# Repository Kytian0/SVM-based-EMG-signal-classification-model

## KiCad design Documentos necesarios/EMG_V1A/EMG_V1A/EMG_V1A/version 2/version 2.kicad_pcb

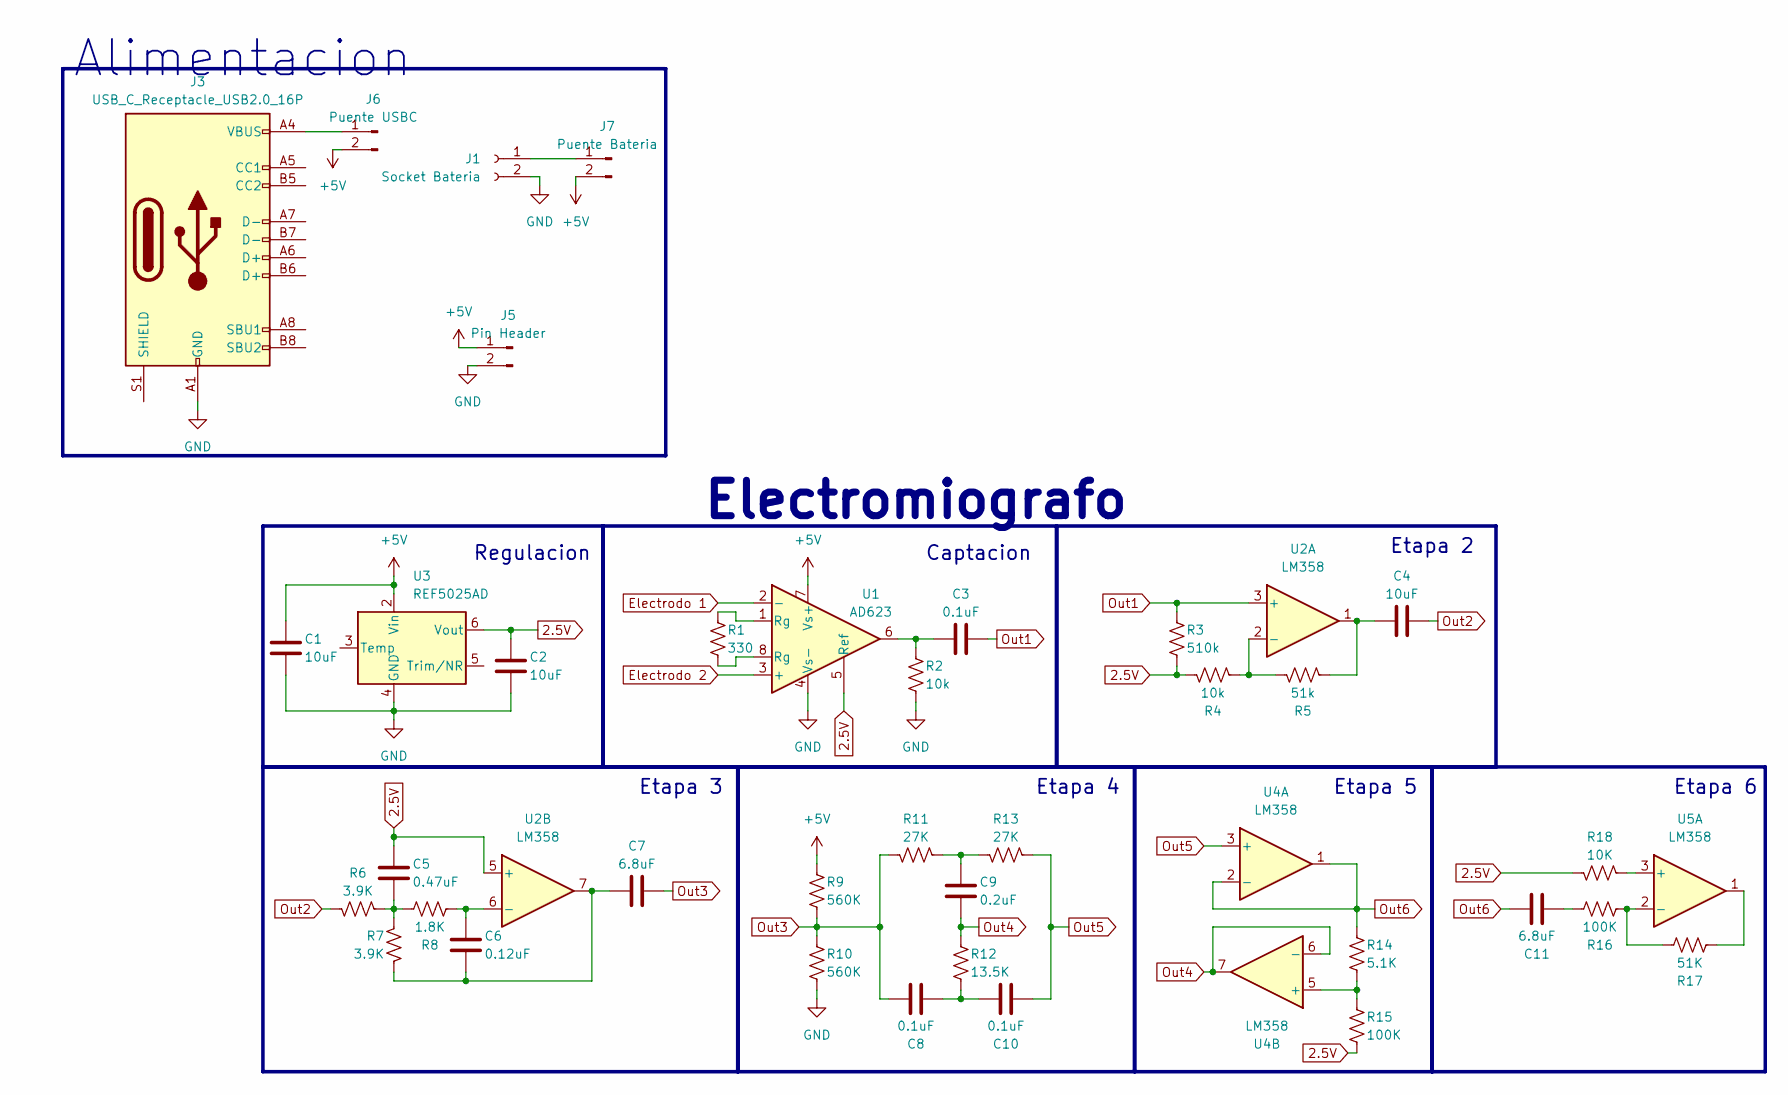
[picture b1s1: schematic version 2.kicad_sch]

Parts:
C1, C2, C4: 10uF; C_Disc_D10.0mm_W2.5mm_P5.00mm
C3, C8, C10: 0.1uF; C_Disc_D10.0mm_W2.5mm_P5.00mm
C5: 0.47uF; C_Disc_D10.0mm_W2.5mm_P5.00mm
C6: 0.12uF; C_Disc_D10.0mm_W2.5mm_P5.00mm
C7, C11: 6.8uF; C_Disc_D10.0mm_W2.5mm_P5.00mm
C9: 0.2uF; C_Disc_D10.0mm_W2.5mm_P5.00mm
J1: Socket Bateria; JST_EH_S2B-EH_1x02_P2.50mm_Horizontal
J3: USB_C_Receptacle_USB2.0_16P; USB_C_Receptacle_GCT_USB4110
J5: Pin Header; PinHeader_1x02_P2.54mm_Vertical
J6: Puente USBC; PinHeader_1x02_P2.54mm_Vertical
J7: Puente Bateria; PinHeader_1x02_P2.54mm_Vertical
R1: 330; R_Axial_DIN0207_L6.3mm_D2.5mm_P10.16mm_Horizontal
R2, R4: 10k; R_Axial_DIN0207_L6.3mm_D2.5mm_P10.16mm_Horizontal
R3: 510k; R_Axial_DIN0207_L6.3mm_D2.5mm_P10.16mm_Horizontal
R5: 51k; R_Axial_DIN0207_L6.3mm_D2.5mm_P10.16mm_Horizontal
R6, R7: 3.9K; R_Axial_DIN0207_L6.3mm_D2.5mm_P10.16mm_Horizontal
R8: 1.8K; R_Axial_DIN0207_L6.3mm_D2.5mm_P10.16mm_Horizontal
R9, R10: 560K; R_Axial_DIN0207_L6.3mm_D2.5mm_P10.16mm_Horizontal
R11, R13: 27K; R_Axial_DIN0207_L6.3mm_D2.5mm_P10.16mm_Horizontal
R12: 13.5K; R_Axial_DIN0207_L6.3mm_D2.5mm_P10.16mm_Horizontal
R14: 5.1K; R_Axial_DIN0207_L6.3mm_D2.5mm_P10.16mm_Horizontal
R15, R16: 100K; R_Axial_DIN0207_L6.3mm_D2.5mm_P10.16mm_Horizontal
R17: 51K; R_Axial_DIN0207_L6.3mm_D2.5mm_P10.16mm_Horizontal
R18: 10K; R_Axial_DIN0207_L6.3mm_D2.5mm_P10.16mm_Horizontal
U1: AD623; DIP-8_W7.62mm_Socket_LongPads
U2: LM358; DIP-8_W7.62mm_LongPads
U3: REF5025AD; SOIC-8_3.9x4.9mm_P1.27mm
U4, U5: LM358; DIP-8_W7.62mm_Socket_LongPads

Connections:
2.5V: C2.1, C5.1, R3.2, R4.2, R15.2, R18.1, U1.5 (Ref), U2.5 (+), U3.6 (Vout)
+5V: C1.1, J5.1, J6.2, J7.2, R9.1, U1.7 (Vs+), U2.8 (V+), U3.2 (Vin), U4.8 (V+), U5.8 (V+)
Electrodo 1: U1.2 (-)
Electrodo 2: U1.3 (+)
GND: C1.2, C2.2, J1.2, J3.A1 (GND), J3.A12 (GND), J3.B1 (GND), J3.B12 (GND), J5.2, R2.2, R10.2, U1.4 (Vs-), U2.4 (V-), U3.4 (GND), U4.4 (V-), U5.4 (V-)
unnamed: C3.1, R2.1, U1.6
unnamed: C4.1, R5.1, U2.1
unnamed: C5.2, R6.2, R7.1, R8.1
unnamed: C6.2, C7.1, R7.2, U2.7
unnamed: C9.1, R11.2, R13.1
unnamed: C8.2, C10.1, R12.2
unnamed: C11.2, R16.1
unnamed: J1.1, J7.1
unnamed: J3.A4 (VBUS), J3.A9 (VBUS), J3.B4 (VBUS), J3.B9 (VBUS), J6.1
unnamed: R1.1, U1.1 (Rg)
unnamed: R1.2, U1.8 (Rg)
unnamed: R17.2, U5.1
unnamed: R4.1, R5.2, U2.2 (-)
unnamed: C6.1, R8.2, U2.6 (-)
unnamed: R14.2, R15.1, U4.5 (+)
unnamed: R18.2, U5.3 (+)
unnamed: R16.2, R17.1, U5.2 (-)
Out1: C3.2, R3.1, U2.3 (+)
Out2: C4.2, R6.1
Out3: C7.2, C8.1, R9.2, R10.1, R11.1
Out4: C9.2, R12.1, U4.6 (-), U4.7
Out5: C10.2, R13.2, U4.3 (+)
Out6: C11.1, R14.1, U4.1, U4.2 (-)

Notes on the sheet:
Etapa 3
Regulacion
Alimentacion
Captacion
Etapa 6
Etapa 5
Etapa 4
Etapa 2
Electromiografo

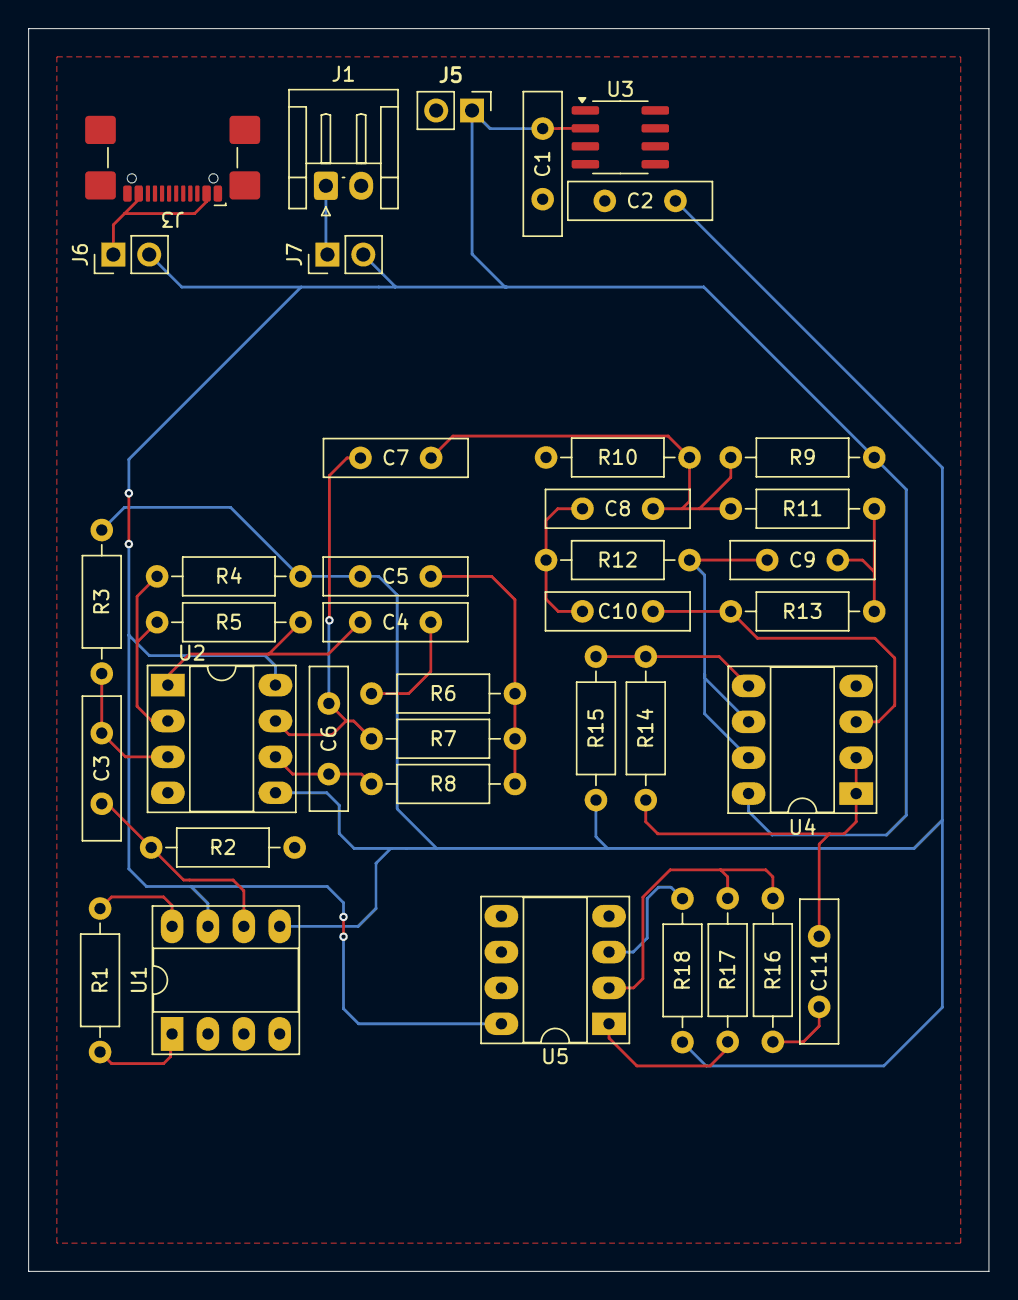
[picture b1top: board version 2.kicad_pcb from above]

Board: 2 copper layers, 68.0 x 88.0 mm, 39 parts (0 on the bottom side), 26 nets.

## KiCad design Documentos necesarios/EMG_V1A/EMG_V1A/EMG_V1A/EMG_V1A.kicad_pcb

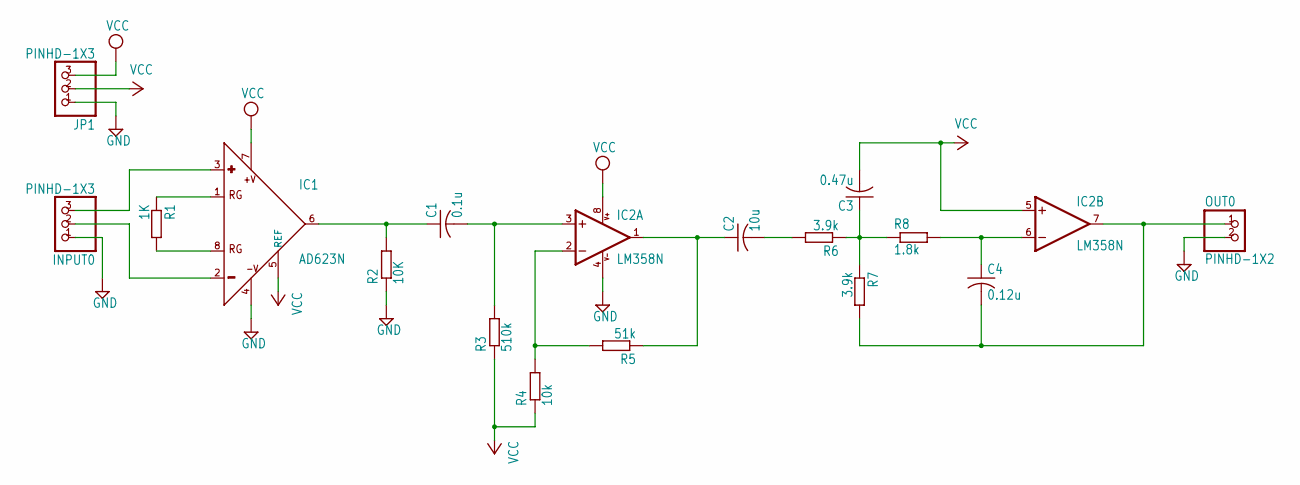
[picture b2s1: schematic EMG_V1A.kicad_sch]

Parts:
C1: 0.1u; C050-030X075
C2: 10u; C050-030X075
C3: 0.47u; C050-030X075
C4: 0.12u; C050-030X075
IC1: AD623N; DIL08
IC2: LM358N; DIL08
INPUT0: PINHD-1X3; 1X03
JP1: PINHD-1X3; 1X03
OUT0: PINHD-1X2; 1X02
R1: 1K; 0204_7
R2: 10K; 0204_7
R3: 510k; 0204_7
R4: 10k; 0204_7
R5: 51k; 0204_7
R6, R7: 3.9k; 0204_7
R8: 1.8k; 0204_7

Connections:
GND: IC1.4 (-V), IC2.4 (V-), INPUT0.1, JP1.1, OUT0.2, R2.1
unnamed: IC1.1 (RG@1), R1.1
unnamed: IC1.8 (RG@2), R1.2
unnamed: IC1.3 (+), INPUT0.3
unnamed: IC1.2 (-), INPUT0.2
unnamed: C1.1, IC1.6 (OUT), R2.2
unnamed: C1.2, IC2.3 (+IN), R3.2
unnamed: IC2.2 (-IN), R4.2, R5.2
unnamed: C2.2, R6.2
unnamed: C2.1, IC2.1 (OUT), R5.1
unnamed: C3.1, R6.1, R7.1, R8.1
unnamed: C4.1, IC2.6 (-IN), R8.2
unnamed: C4.2, IC2.7 (OUT), OUT0.1, R7.2
VCC: C3.2, IC1.5 (REF), IC1.7 (+V), IC2.5 (+IN), IC2.8 (V+), JP1.2, JP1.3, R3.1, R4.1

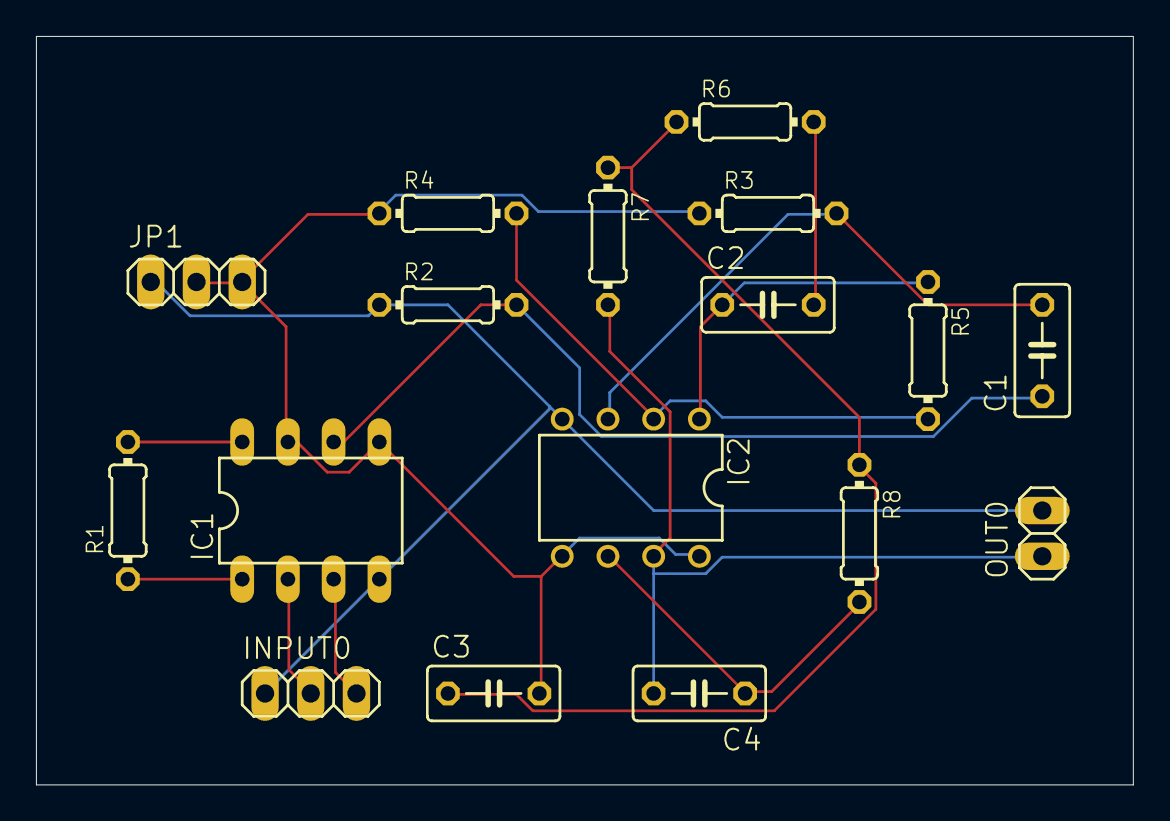
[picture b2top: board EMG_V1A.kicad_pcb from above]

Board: 2 copper layers, 60.9 x 41.6 mm, 17 parts (0 on the bottom side), 14 nets.
